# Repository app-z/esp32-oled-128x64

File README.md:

# esp32-oled-128x64
esp32 dev board PCB with oled display 128x64

https://habr.com/ru/topic/edit/485402/

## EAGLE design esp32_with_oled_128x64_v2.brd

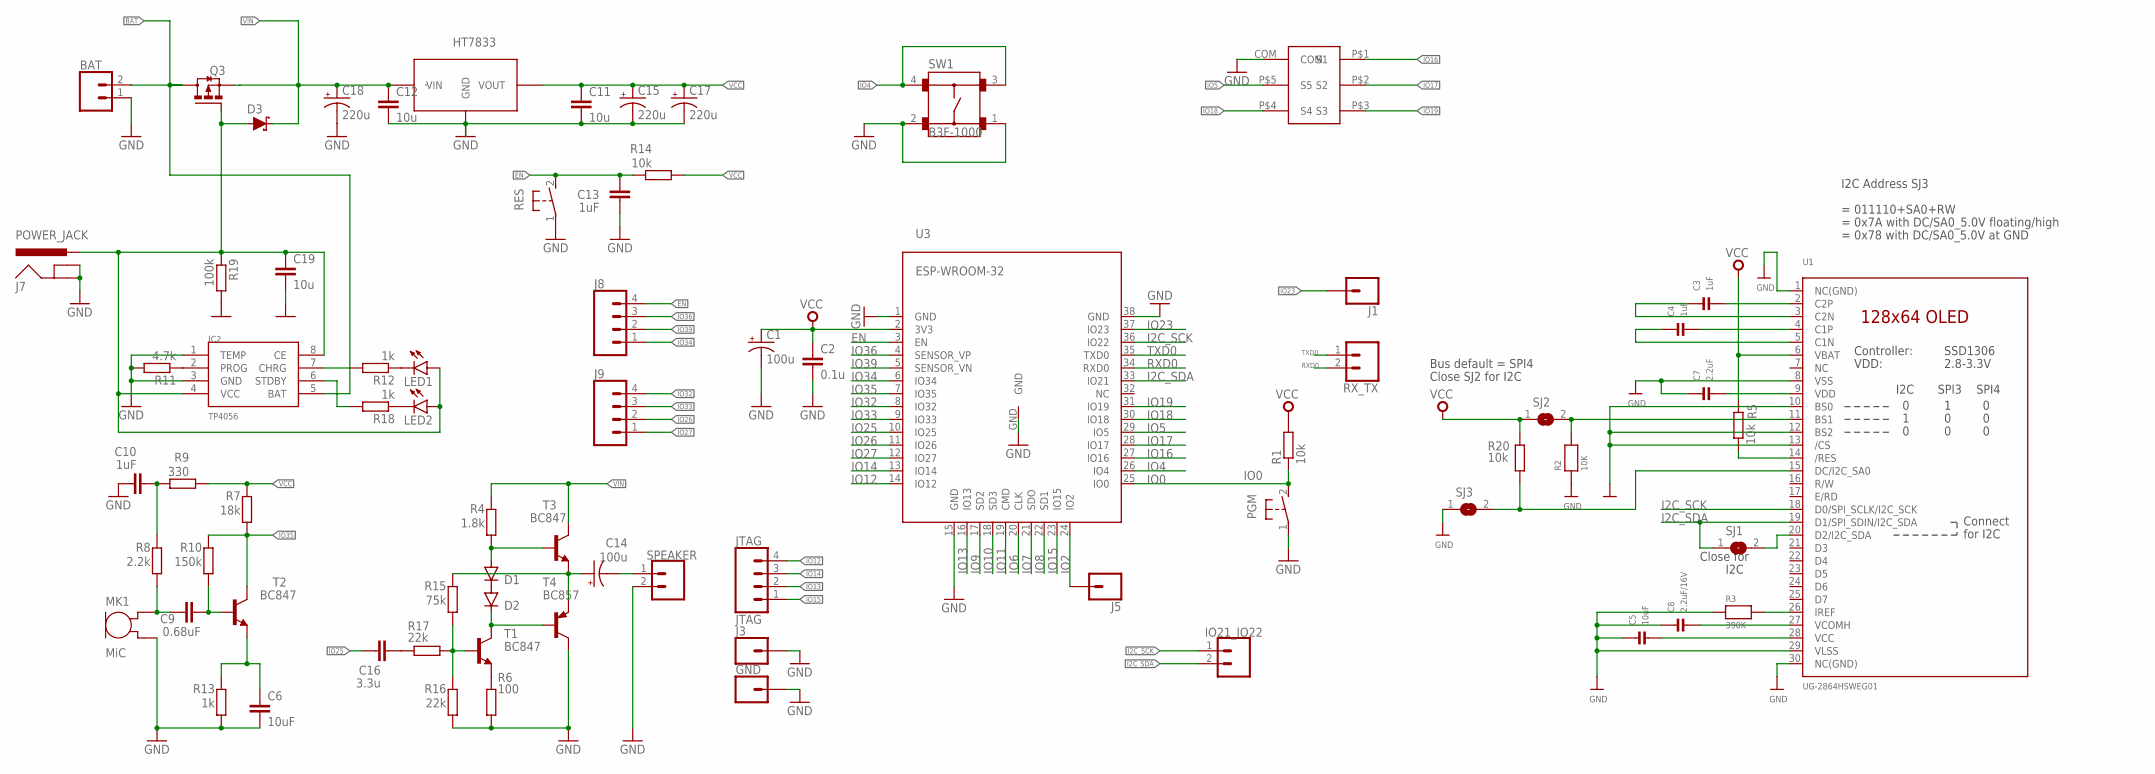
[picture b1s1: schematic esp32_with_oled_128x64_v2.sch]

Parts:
BAT: CONN_02; 1X02
C1: 100u; VISHAY_C
C2: 0.1u; 0805
C3, C4, C10, C13: 1uF; 0805
C5, C6: 10uF; 0805
C7: 2.2uF; 0805
C8: 2.2uF/16V; 0805
C9: 0.68uF; 0805
C11, C12, C19: 10u; C0805K
C14: 100u; CPOL-RADIAL-100UF-25V
C15, C17, C18: 220u; CPOL-RADIAL-100UF-25V
C16: 3.3u; 0805
D1, D2: DIODE-SOD323-W; SOD323-W
D3: DIODE-SCHOTTKY-BAT20J; SOD-323
GND: CONN_01; 1X01
IC2: TP4056; SOP-8
IO21_IO22: CONN_02; 1X02
J1, J3, J5: CONN_01; 1X01
J7: POWER_JACK; POWER_JACK_PTH
J8, J9: CONN_04; 1X04
JTAG: JTAG; 1X04
LED1: LED3MM
LED2: LEDCHIP-LED0805; CHIP-LED0805
MK1: MiC; CMA-4544PF-W
PGM: DTSM-3
Q3: FDN360P; SUPER-SOT3
R1, R5, R14, R20: 10k; R0805
R2: 10K; 0805_NOTHERMALS
R3: 390K; 0805_NOTHERMALS
R4: 1.8k; R0805
R6: 100; R0805
R7: 18k; R0805
R8: 2.2k; R0805
R9: 330; R0805
R10: 150k; R0805
R11: 4.7k; R0805
R12, R13, R18: 1k; R0805
R15: 75k; R0805
R16, R17: 22k; R0805
R19: 100k; R0805
RES: DTSM-3
RX_TX: CONN_02; 1X02
SJ1, SJ2, SJ3: SOLDERJUMPERREFLOW_NOPASTE; SOLDERJUMPER_REFLOW_NOPASTE
SPEAKER: CONN_02; 1X02
SW1: B3F-1000
T1, T2, T3: BC847; SOT23
T4: BC857; SOT23-BEC
U1: UG-2864HSWEG01; UG-2864HSWEG01_0.96IN_WRAPAROUND
U3: ESP-WROOM-32
U$1: DJOYSTICK-MY; DJOYSTIC-MY
U$3: HT7833; SOT89

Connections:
BAT: BAT.2, IC2.5 (BAT), Q3.3 (D)
EN: C13.2, J8.4, R14.2, RES.2, U3.3 (EN)
GND: BAT.1, C1.-, C2.2, C5.1, C6.2, C7.1, C8.1, C10.1, C11.2, C12.2, C13.1, C15.2 (-), C17.2 (-), C18.2 (-), C19.2, GND.1, IC2.1 (TEMP), IC2.3 (GND), J3.1, J7.GND, J7.GNDBREAK, MK1.2 (GND), PGM.1, R2.1, R3.1, R6.1, R11.2, R13.1, R16.1, R19.2, RES.1, SJ3.1, SPEAKER.2, SW1.1, SW1.2, T4.C, U1.1 (NC(GND)), U1.8 (VSS), U1.10 (BS0), U1.12 (BS2), U1.13 (/CS), U1.29 (VLSS), U1.30 (NC(GND)), U3.1 (GND), U3.15 (GND), U3.38 (GND), U3.GND, U$1.COM, U$3.GND
I2C_SCK: IO21_IO22.1, U1.18 (D0/SPI_SCLK/I2C_SCK), U3.36 (IO22)
I2C_SDA: IO21_IO22.2, SJ1.1, U1.19 (D1/SPI_SDIN/I2C_SDA), U3.33 (IO21)
IO0: PGM.2, R1.1, U3.25 (IO0)
IO2: J5.1, U3.24 (IO2)
IO4: SW1.3, SW1.4, U3.26 (IO4)
IO5: U3.29 (IO5), U$1.P$5 (S5)
IO6: U3.20 (CLK)
IO7: U3.21 (SDO)
IO8: U3.22 (SD1)
IO9: U3.17 (SD2)
IO10: U3.18 (SD3)
IO11: U3.19 (CMD)
IO12: JTAG.4, U3.14 (IO12)
IO13: JTAG.2, U3.16 (IO13)
IO14: JTAG.3, U3.13 (IO14)
IO15: JTAG.1, U3.23 (IO15)
IO16: U3.27 (IO16), U$1.P$1 (S1)
IO17: U3.28 (IO17), U$1.P$2 (S2)
IO18: U3.30 (IO18), U$1.P$4 (S4)
IO19: U3.31 (IO19), U$1.P$3 (S3)
IO23: J1.1, U3.37 (IO23)
IO25: C16.1, U3.10 (IO25)
IO26: J9.2, U3.11 (IO26)
IO27: J9.1, U3.12 (IO27)
IO32: J9.4, U3.8 (IO32)
IO33: J9.3, U3.9 (IO33)
IO34: J8.1, U3.6 (IO34)
IO35: R7.1, R10.2, T2.3 (C), U3.7 (IO35)
IO36: J8.3, U3.4 (SENSOR_VP)
IO39: J8.2, U3.5 (SENSOR_VN)
unnamed: R2.2, SJ2.2, U1.11 (BS1)
unnamed: SJ1.2, U1.20 (D2/I2C_SDA)
unnamed: R3.2, U1.26 (IREF)
unnamed: C3.2, U1.2 (C2P)
unnamed: C3.1, U1.3 (C2N)
unnamed: C4.2, U1.4 (C1P)
unnamed: C4.1, U1.5 (C1N)
unnamed: C19.1, D3.A, IC2.4 (VCC), IC2.8 (CE), J7.PWR, LED1.A, LED2.A, Q3.1 (G), R19.1
unnamed: C14.2 (-), SPEAKER.1
unnamed: C16.2, R17.2
unnamed: C5.2, U1.28 (VCC)
unnamed: C8.2, U1.27 (VCOMH)
unnamed: D1.A, R4.1, T3.1 (B)
unnamed: C6.1, R13.2, T2.2 (E)
unnamed: C9.2, R10.1, T2.1 (B)
unnamed: C10.2, R8.2, R9.2
unnamed: C9.1, MK1.1 (OUT), R8.1
unnamed: D2.C, T1.3 (C), T4.B
unnamed: IC2.2 (PROG), R11.1
unnamed: R15.1, R16.2, R17.1, T1.1 (B)
unnamed: LED1.K (C), R12.1
unnamed: IC2.7 (CHRG), R12.2
unnamed: D1.C, D2.A
unnamed: R6.2, T1.2 (E)
unnamed: C14.1 (+), R15.2, T3.2 (E), T4.E
unnamed: LED2.C, R18.1
unnamed: IC2.6 (STDBY), R18.2
unnamed: R20.2, SJ3.2, U1.15 (DC/I2C_SA0)
unnamed: R5.1, U1.14 (/RES)
RXD0: RX_TX.2, U3.34 (RXD0)
TXD0: RX_TX.1, U3.35 (TXD0)
VCC: C1.+, C2.1, C7.2, C11.1, C15.1 (+), C17.1 (+), R1.2, R5.2, R7.2, R9.1, R14.1, R20.1, SJ2.1, U1.6 (VBAT), U1.9 (VDD), U3.2 (3V3), U$3.VOUT
VIN: C12.1, C18.1 (+), D3.C, Q3.2 (S), R4.2, T3.3 (C), U$3.VIN

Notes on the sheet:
Bus default = SPI4
Close SJ2 for I2C
= 011110+SA0+RW
= 0x7A with DC/SA0_5.0V floating/high
= 0x78 with DC/SA0_5.0V at GND
I2C Address SJ3
Close for
I2C

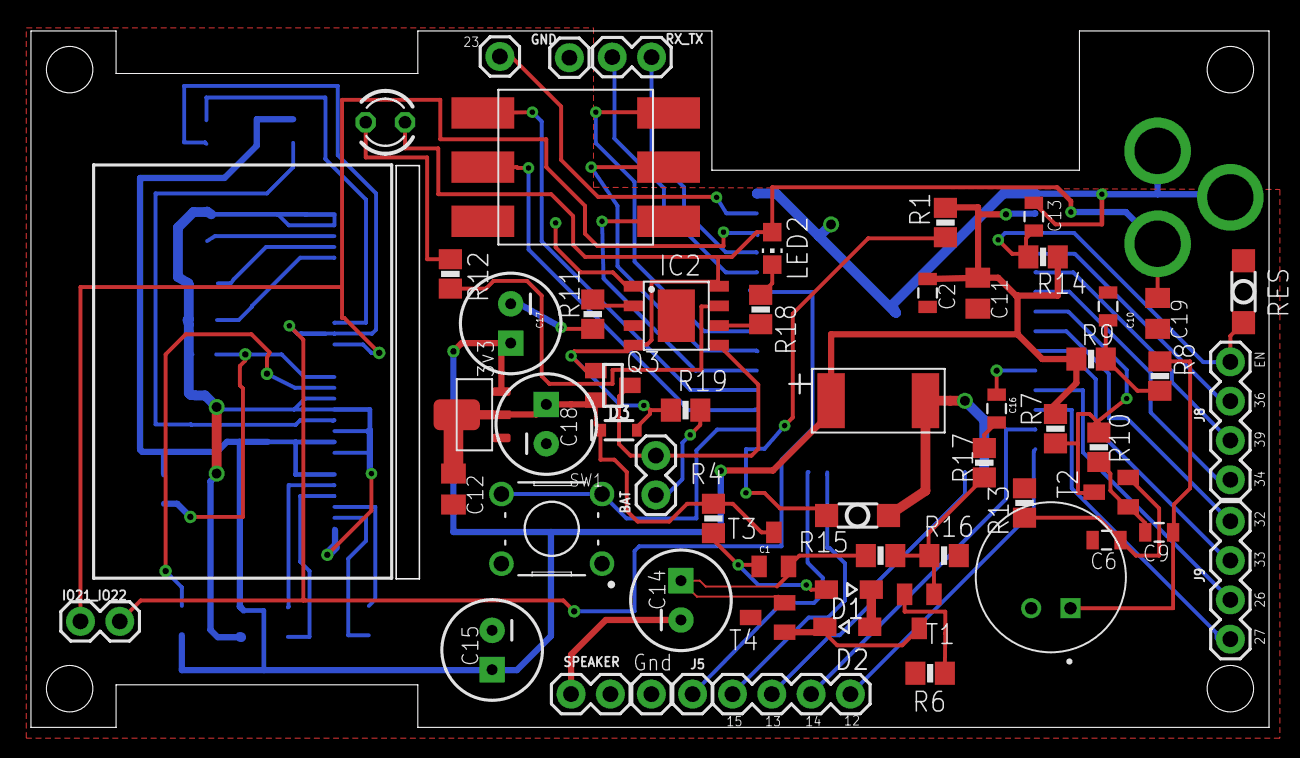
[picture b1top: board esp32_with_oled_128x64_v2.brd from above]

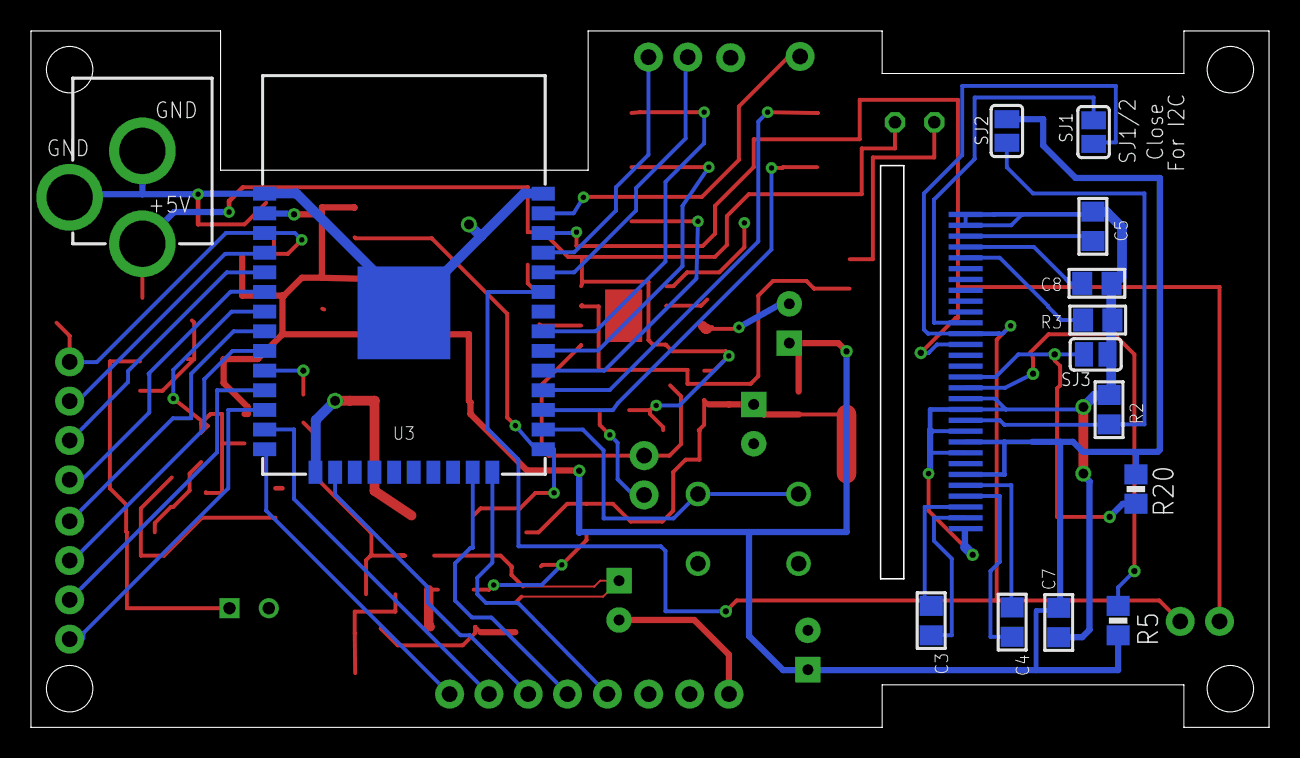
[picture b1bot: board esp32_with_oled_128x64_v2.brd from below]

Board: 2 copper layers, 79.9 x 44.9 mm, 73 parts (14 on the bottom side), 60 nets.

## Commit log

2020-02-16 Autodesk Eagle schema
2020-02-16 Autodesk Eagle PCB

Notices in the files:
parts and their libraries:
SparkFun-Passives: Licensing: Creative Commons ShareAlike 4.0 International - https://creativecommons.org/licenses/by-sa/4.0
esp32_: Creative Commons Attribution-ShareAlike 4.0 International
